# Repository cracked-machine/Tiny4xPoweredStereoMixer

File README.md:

HTML version of this page can be found [here](https://cracked-machine.github.io/Tiny4xPoweredStereoMixer/)

# Tiny 4 Channel Powered Stereo Mixer

A Tiny form-factor 4-channel stereo mixer for use with TV/PC/Turntable/Amplifer

## Requirements

1. 4 stereo inputs
2. 1 stereo output
3. Inputs will all use stereo RCA/Phono connectors
4. volume controls for each of the 4 input channels
5. volume controls should be mounted in the front of the case
6. External power input shall be 9V DC
7. Internal power supply shall be +/-9V DC
8. Input signals shall be buffered
9. Volume controls for each channel shall  be independant and not subtract gain from the other channels.
10. Cross-talk between channels should be minimised.
  
## Top level Design

The opamps shall use [TL072](https://www.ti.com/lit/gpn/TL072H)

Using opamps to buffer the input signals and mix the channels together will ensure that the volume of each channel can be mixed independently from the others.

The design will implement an inverting opamp "virtual  ground" topology. The virtual ground refers to the inputs of the mixing opamp: the non-inverting input will be referenced to ground, which means the voltage at both opamp inputs will be referenced to ground because the potential _difference between inputs_ will always try to be zero. The absence of voltage at these inputs will prevent cross-talk between the channels. There is a far superior explanation of this concept at [sound-au.com](https://sound-au.com/articles/audio-mixing.htm#s3)

## Power Stage Design

The old PSU design for Rev A/B can be found in [OLDPSU.md](OLDPSU.md).

The negative voltage rail is generated from the positive rail using a [TPS54202](https://www.ti.com/lit/ds/symlink/tps54202.pdf) SMPS IC. This is normally a buck regulator. However, it can be configured to generate a negative voltage when pin 2 is clamped to ground, forcing pin 1 to a negative voltage.

Further details can be found in the [SLVA933](https://www.ti.com/lit/an/slva933/slva933.pdf) app note

### Soft Start

Unlike the LM2611, the TPS54202 has an internal soft start circuit. This can be seen in the Function Block Diagram of the [TPS54202](https://www.ti.com/lit/ds/symlink/tps54202.pdf) datasheet.

### Output Voltage 

Output voltage is selected using the voltage divider between pins 2 and 1, creating feedback into pin 4. This is very similar to the normal operation of this IC.

### Current Draw and Load Regulation

Output ripple is shown in the [SLVA933](https://www.ti.com/lit/an/slva933/slva933.pdf) app note as 5mV at no load and 20mV at 0.8A (see pages 21-22).

For my own test I [created a small board](https://github.com/cracked-machine/tps54202_inverting_breakout).
The original layout example with the new configuration violated the layout guiidelines from the [TPS54202](https://www.ti.com/lit/ds/symlink/tps54202.pdf) datasheet and proved to be noisy (240mV @ 0.6A). A second revision was made with a better layout that observed the guideline and was a significant improvement (80mv @ 0.6A).

Load regulation was around 5%, dropping from 12V to 11.4V @ 0.6A.

These results were acceptable so this PSU design was used.

## Schematics

<object data="doc/design/Tiny4xPoweredStereoMixer.pdf" type="application/pdf" width="100%" height="1000px">
    <embed src="doc/design/Tiny4xPoweredStereoMixer.pdf">
        <p>This browser does not support PDFs. Please download the PDF to view it: <a href="doc/design/Tiny4xPoweredStereoMixer.pdf">Download PDF</a>.</p>
    </embed>
</object>

## Layout

I used a 4 layer board so I could have a layer per voltage rail. This makes routing the traces significantly easier. I kept the board dimensions below 10cm to minimize manufacture costs. 

[Interactive BOM](https://cracked-machine.github.io/Tiny4xPoweredStereoMixer/doc/design/ibom.html)

## Enclosure

I abandoned the 3D printed enclosure idea and made the PCB to fit this [Hammond RM2005MTBK](https://www.hammfg.com/part/RM2005MTBK) clam shell enclosure.

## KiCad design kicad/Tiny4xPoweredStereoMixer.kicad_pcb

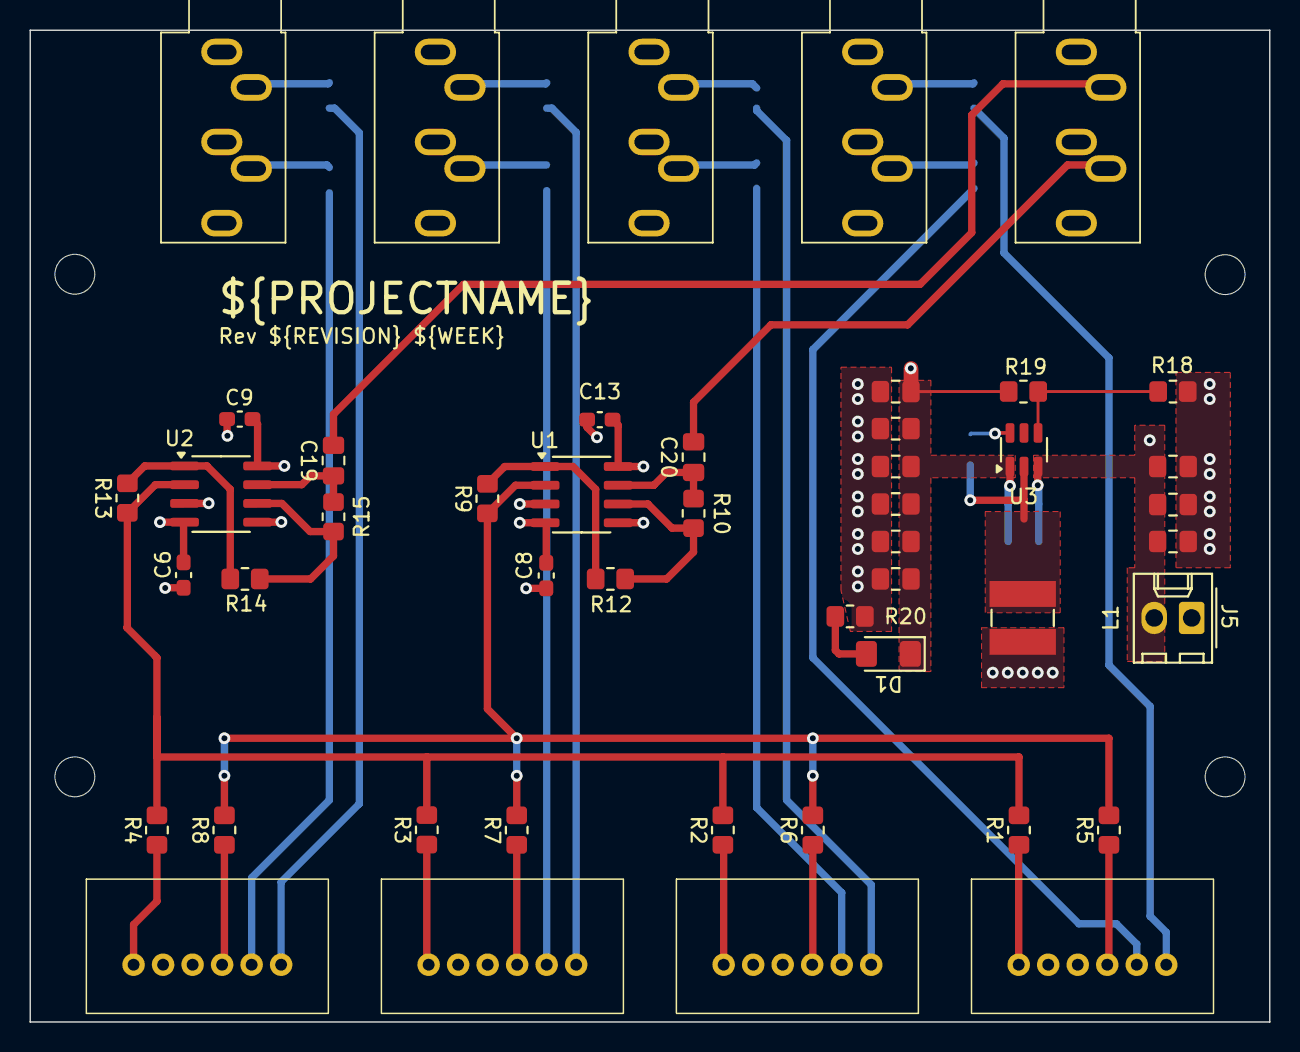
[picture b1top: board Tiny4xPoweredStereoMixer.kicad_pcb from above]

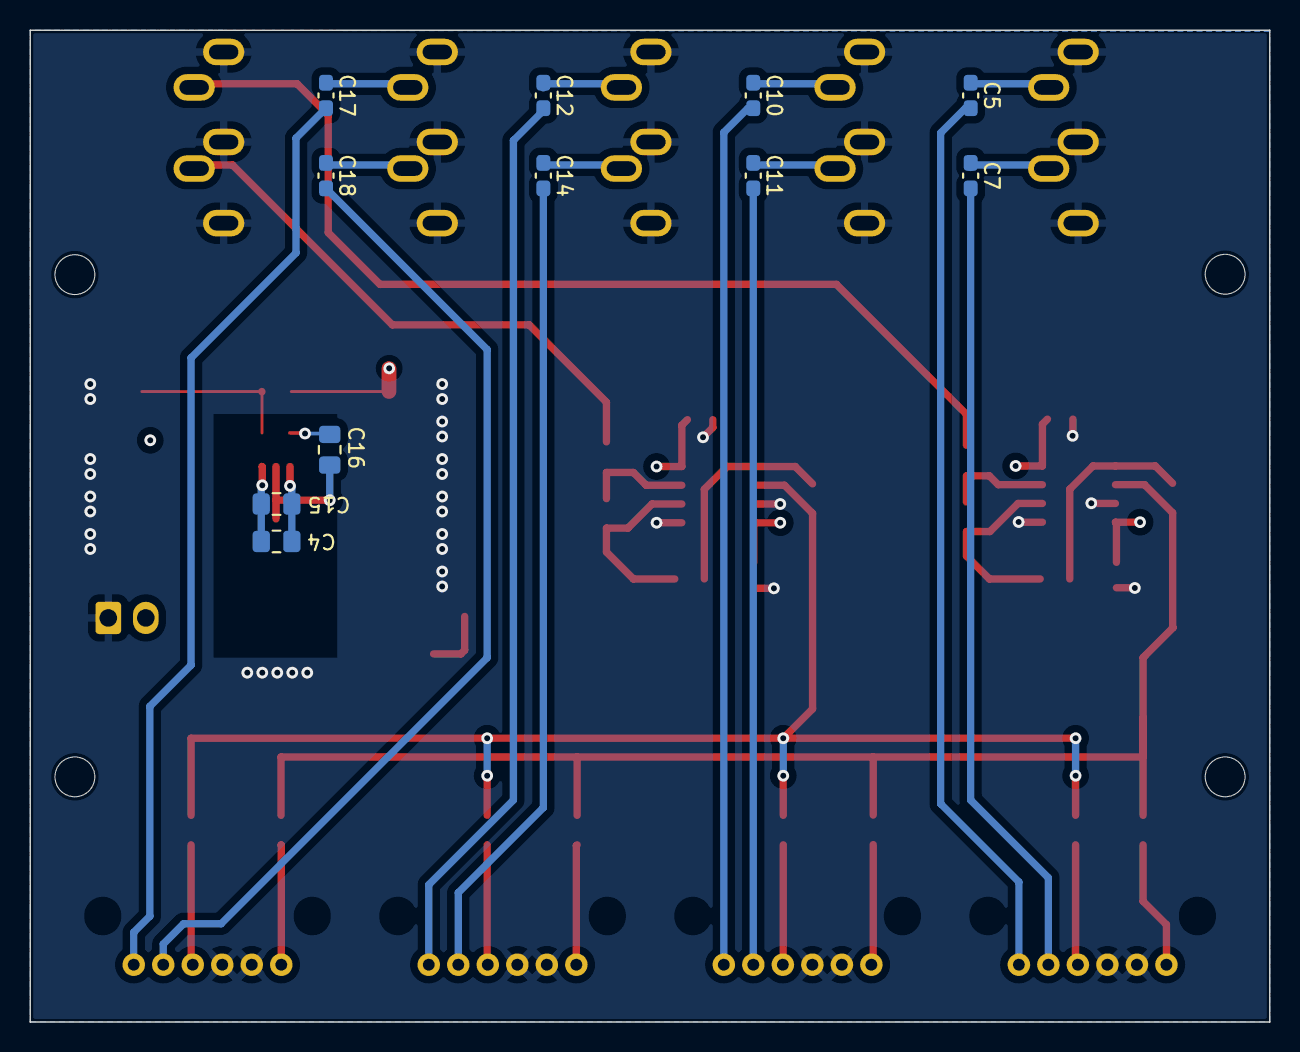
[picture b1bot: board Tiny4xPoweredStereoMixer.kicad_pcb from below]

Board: 4 copper layers, 84.0 x 67.2 mm, 62 parts (11 on the bottom side), 41 nets.

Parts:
C1, C2, C15, C19, C20: 10uF; C_0805_2012Metric_Pad1.18x1.45mm_HandSolder
C3, C4, C16, C21: 100nF; C_0805_2012Metric_Pad1.18x1.45mm_HandSolder
C5, C6, C7, C8, C9, C10, C11, C12, C13, C14, C17, C18: 100nF; C_0603_1608Metric_Pad1.08x0.95mm_HandSolder
C22, C23, C24, C25, C26: 22uF; C_0805_2012Metric_Pad1.18x1.45mm_HandSolder
D1: LED; LED_1206_3216Metric_Pad1.42x1.75mm_HandSolder
H1, H2, H3, H4: MountingHole; MountingHole_2.7mm_M2.5
J1, J2, J3, J4, J9: AudioJack3_SwitchTR; Jack_3.5mm_CUI_SJ1-3535NG_Horizontal
J5: PowerConnector; Molex_KK-254_AE-6410-02A_1x02_P2.54mm_Vertical
L1: 22uH; L_Ferrocore_DLG-0403
R1, R2, R3, R4, R5, R6, R7, R8, R9, R10, R12, R13, R14, R15: 10k; R_0805_2012Metric_Pad1.20x1.40mm_HandSolder
R18: 50K; R_0805_2012Metric_Pad1.20x1.40mm_HandSolder
R19: 6K8; R_0805_2012Metric_Pad1.20x1.40mm_HandSolder
R20: 2K2; R_0805_2012Metric_Pad1.20x1.40mm_HandSolder
RV1, RV2, RV3, RV4: 10k; Alps_RK12L12_Double_Horizontal
U1, U2: TL072; SOIC-8_3.9x4.9mm_P1.27mm
U3: TPS54202DDC; SOT-23-6

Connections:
+5V: C1.1, C2.1, C3.1, C4.1, C9.1, C13.1, C15.1, J5.2, U1.8 (V+), U2.8 (V+), U3.3 (VIN)
-5V: C4.2, C6.1, C8.1, C15.2, C21.2, C22.2, C23.2, C24.2, C25.2, C26.2, D1.1 (K), R19.1, U1.4 (V-), U2.4 (V-), U3.1 (GND)
/TPS54202 Inverting PSU/VSENSE: R18.1, R19.2, U3.4 (FB)
/ch1_left_mix_in: R4.1, RV1.5
/ch1_right_mix_in: R8.1, RV1.2
/ch2_left_mix_in: R3.1, RV2.5
/ch2_right_mix_in: R7.1, RV2.2
/ch3_left_mix_in: R2.1, RV3.5
/ch3_right_mix_in: R6.1, RV3.2
/ch4_left_mix_in: R1.1, RV4.5
/ch4_right_mix_in: R5.1, RV4.2
GND: C1.2, C2.2, C3.2, C6.2, C8.2, C9.2, C13.2, C21.1, C22.1, C23.1, C24.1, C25.1, C26.1, J1.RN, J1.S, J1.TN, J2.RN, J2.S, J2.TN, J3.RN, J3.S, J3.TN, J4.RN, J4.S, J4.TN, J5.1, J9.RN, J9.S, J9.TN, L1.2, R18.2, R20.2, RV1.1, RV1.4, RV2.1, RV2.4, RV3.1, RV3.4, RV4.1, RV4.4, U1.3 (+), U1.5 (+), U2.3 (+), U2.5 (+)
unnamed: C5.1, J1.T
unnamed: C5.2, RV1.6
unnamed: C7.1, J1.R
unnamed: C7.2, RV1.3
unnamed: C10.1, J2.T
unnamed: C10.2, RV2.6
unnamed: C11.1, J2.R
unnamed: C11.2, RV2.3
unnamed: C12.1, J3.T
unnamed: C12.2, RV3.6
unnamed: C14.1, J3.R
unnamed: C14.2, RV3.3
unnamed: C17.1, J4.T
unnamed: C17.2, RV4.6
unnamed: C18.1, J4.R
unnamed: C18.2, RV4.3
unnamed: C19.1, R15.2, U2.7
unnamed: C19.2, J9.T
unnamed: C20.1, R10.2, U1.7
unnamed: C20.2, J9.R
unnamed: D1.2 (A), R20.1
unnamed: R9.2, R12.1, U1.1
unnamed: R13.2, R14.1, U2.1
unnamed: R5.2, R6.2, R7.2, R8.2, R9.1, U1.2 (-)
unnamed: R10.1, R12.2, U1.6 (-)
unnamed: R1.2, R2.2, R3.2, R4.2, R13.1, U2.2 (-)
unnamed: R14.2, R15.1, U2.6 (-)
unnamed: C16.1, U3.6 (BOOT)
unnamed: C16.2, L1.1, U3.2 (SW)

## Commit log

2024-03-15 Create LICENSE
2024-03-15 BlockDiagram.drawio
2024-03-15 Rename Untitled Diagram.drawio to BlockDiagram.drawio
2024-03-15 Added requirements
2024-03-15 Added requirement
2024-03-15 Added BlockDiagram.drawio.png
2024-03-16 Moved BlockDiagram.drawio.png
2024-03-16 Increased block lines in BlockDiagram.drawio.png
2024-03-16 white backgtround in BlockDiagram.drawio.png
2024-03-16 Added BlockDiagram.png
2024-03-16 upload kicad project
2024-03-16 switched slashes
2024-03-16 increased embedded pdf width and height to 1000px
2024-03-16 increased embed pdf width to 100%
2024-03-16 added gtihub pages link
2024-03-16 Create _config.yml
    trying minimal theme
2024-03-16 Update _config.yml
    Testing slate theme
2024-03-17 main schematic done, layout started
2024-03-17 saved
2024-03-17 added barrel jack connector to schema
2024-03-17 added connectors/jumper for isolating the +/-12V power lines
2024-03-17 updated powerflags
2024-03-17 ignore lock file
2024-03-17 add mount holes
2024-03-17 positioned +/-12v connectors
2024-03-17 completed reva layout
2024-03-17 updated pdf schematic
2024-03-17 added ibom
2024-03-22 Added System Context Diagram.drawio
2024-03-22 Rename Untitled Diagram.drawio to SystemContextDiagram.drawio
2024-03-22 Added SystemContextDiagram.drawio.png
2024-03-31 updated cuk converter negative feedback resistors
2024-03-31 - Fixed in-rush current problem using soft-start design. https://github.com/cracked-machine/Tiny4xPoweredStereoMixer/issues/4 - Fixed reversed pots. https://github.com/cracked-machine/Tiny4xPoweredSt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
2024-03-31 Added BlockDiagram2.drawio.png
2024-03-31 Refactored schematic into single page (except PSU)
2024-03-31 updated schematics
2024-04-01 added RK12L2 pot footprint
2024-04-01 updated RK12l12
2024-04-01 - updated pots to rk12l12
2024-04-01 replaced phono connectors with 3.5mm stereo jack connectors so that unplugged connections are switched to ground
2024-04-01 completed revb layout
2024-04-01 Replaced raw load reg data with graph
2024-04-13 updated ibom
2024-04-13 updated schematic pdf
2024-04-13 updated pcb layout project file
2024-04-18 updated schematic to use TPS54202
2024-10-21 Added extra output capacitor footprints to psu
2024-10-21 Set PCB rules and edded outline for Hammond RM2005S enclosure
2024-10-22 Finished RevC layout
2024-10-23 changed pot from linear to log
2024-11-05 rev c layout complete
2024-11-05 updated docs
2024-11-05 updated main
2024-11-05 Update README.md
    slashes
2024-11-23 PSU now uses +/- 2.5V; Added barrel jack; updated layout
2024-11-23 Created missing SOT-23-THIN-14 footprint; Replaced 2xTL072 with 1xTL074; updated layout
2024-11-24 changed voltage rails to +/-5V; changed PSU feedback resistor to provide -5V
2024-11-24 Revert "changed voltage rails to +/-5V; changed PSU feedback resistor to provide -5V"
    This reverts commit 87719da26a309bbde2d2f76146bcb1e510287c62.
